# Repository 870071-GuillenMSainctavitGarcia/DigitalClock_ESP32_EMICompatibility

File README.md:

# DigitalClock_ESP32_EMICompatibility

A 2-layer custom hardware board designed in **KiCad 9.0** featuring dual isolated ground planes (`GND` and `GND1`), input noise filtering, an onboard 12V-to-5V buck regulator, and Wi-Fi capabilities for acquiring UTC time via NTP.

---

##  Features

- **ESP32 Microcontroller:** Integrated module layout with a dedicated antenna exclusion zone to maximize Wi-Fi & Bluetooth RF performance.
- **Dual Isolated Ground Planes:** Independent `GND` and `GND1` domains to prevent noise coupling across high-voltage input and digital control sections.
- **Power Management:**
  - **Input Filtering:** Common Mode Choke & Pi Filter ($C-L-C$) for supply line noise suppression.
  - **Buck Regulator:** High-efficiency $12\text{V} \to 5\text{V}$ DC-DC step-down switching converter (TSOT-23-8 footprint).
- **Peripherals & Debugging:**
  - Onboard I2C sensor interface with pull-up resistors (`SDA` / `SCL`).
  - Strategic Test Points (`12V_TP`, `5V_TP`, `3V3_TP`, `SDA_TP`, `SCL_TP`, `GND_TP`).
- **DFA / DFM Compliant:** 2-layer stackup optimized for JLCPCB manufacturing rules (0.15 mm minimum clearance).

---

##  Hardware Specifications

| Parameter | Value |
| :--- | :--- |
| **Input Voltage** | 12V DC |
| **Regulated Voltages** | 5V DC (Buck Converter Output), 3.3V DC (ESP32 LDO) |
| **PCB Stackup** | 2 Layers (`F.Cu` signal routing & components, `B.Cu` ground plane) |
| **EDA Software** | KiCad 9.0 |
| **Minimum Clearance** | 0.15 mm (6 mil) |
| **Drill Format** | Excellon Merged (PTH + NPTH) |
| **Gerber Format** | Extended Gerber RS-274X (Protel File Extensions) |

---

# PCB and Layout

- **Layer Architecture:**
  - **Top Layer (`F.Cu`):** Primary routing layer for SMD components, power distribution traces, and signal lines.
  - **Bottom Layer (`B.Cu`):** Dedicated low-impedance continuous ground plane for optimal return paths and EMI reduction.
- **Isolated Ground Planes (`GND` vs `GND1`):**
  - **`GND1` Domain:** Isolated ground fill surrounding the $12\text{V}$ power input, protection diode, and Pi filter stage to contain input switching noise.
  - **`GND` Domain:** Main system ground covering the buck regulator output stage, ESP32 module, and digital peripherals.
- **RF Antenna Keepout Zone:**
  - Full copper clearance on all layers directly underneath the ESP32 PCB antenna region to prevent RF attenuation and maintain maximum Wi-Fi/Bluetooth range.
- **Power Routing & Via Placement:**
  - Expanded track widths ($0.8\text{ mm} - 1.2\text{ mm}$) for $12\text{V}$ input, switching nodes, and $5\text{V}$ power rails.
  - Low-inductance ground vias placed in immediate proximity to SMD ground pads for direct bottom-layer stitching.
- **Design Rules (DRC):**
  - Optimized $0.15\text{ mm}$ ($6\text{ mil}$) trace clearance to accommodate high-density TSOT-23-8 IC footprints without manufacturing rule violations.
---

---

# Schematic

The schematic is divided into distinct functional blocks optimized for power integrity, noise isolation, and ease of debugging:

### 1. Power Input & Isolated Domain (`GND1`)
- **Input Terminal:** $12\text{V}$ DC main supply connection (`J2`).
- **Protection Stage:** Schottky diodes (`D1`, `D3`) providing reverse-polarity protection and transient voltage suppression.
- **Noise Filtering:** Dual-stage EMI filtering using a Common Mode Choke (`FL1`) and a Pi Filter ($C-L-C$) to prevent external noise from entering the board.

### 2. Step-Down Buck Converter ($12\text{V} \to 5\text{V}$)
- **Regulator Core:** High-efficiency DC-DC switching regulator (`U1`, TSOT-23-8 footprint).
- **LC Output Filter:** High-current power inductor (`L1`) paired with low-ESR ceramic capacitor banks (`C1`–`C16`) for low output voltage ripple under dynamic loads.

### 3. ESP32 Microcontroller Core (`U2`)
- **Main Processing Unit:** ESP32 module powered from the main $5\text{V}$ rail (converted to $3.3\text{V}$ via internal LDO).
- **Wireless Connectivity:** Optimized for Wi-Fi synchronization to fetch real-time UTC timestamps via NTP servers.

### 4. Sensor & Peripheral Interface
- **I2C Bus:** Dedicated MSOP-8 sensor interface (`U3`) and expansion header (`J3`) with integrated pull-up resistors (`RPullUp-SCL1`, `RPullUp-SDA1`).

### 5. Diagnostic Test Points
- Strategic test pads placed across key nets for oscilloscope and multimeter probing:
  - **Power Rails:** `12V_TP1`, `12VE_TP2`, `5V_TP5`, `3V3_TP7`
  - **Signals:** `SCL_TP9`, `SDA_TP8`
  - **Ground References:** `GND_TP3`, `GND_TP4`, `GND1_TP10`
---

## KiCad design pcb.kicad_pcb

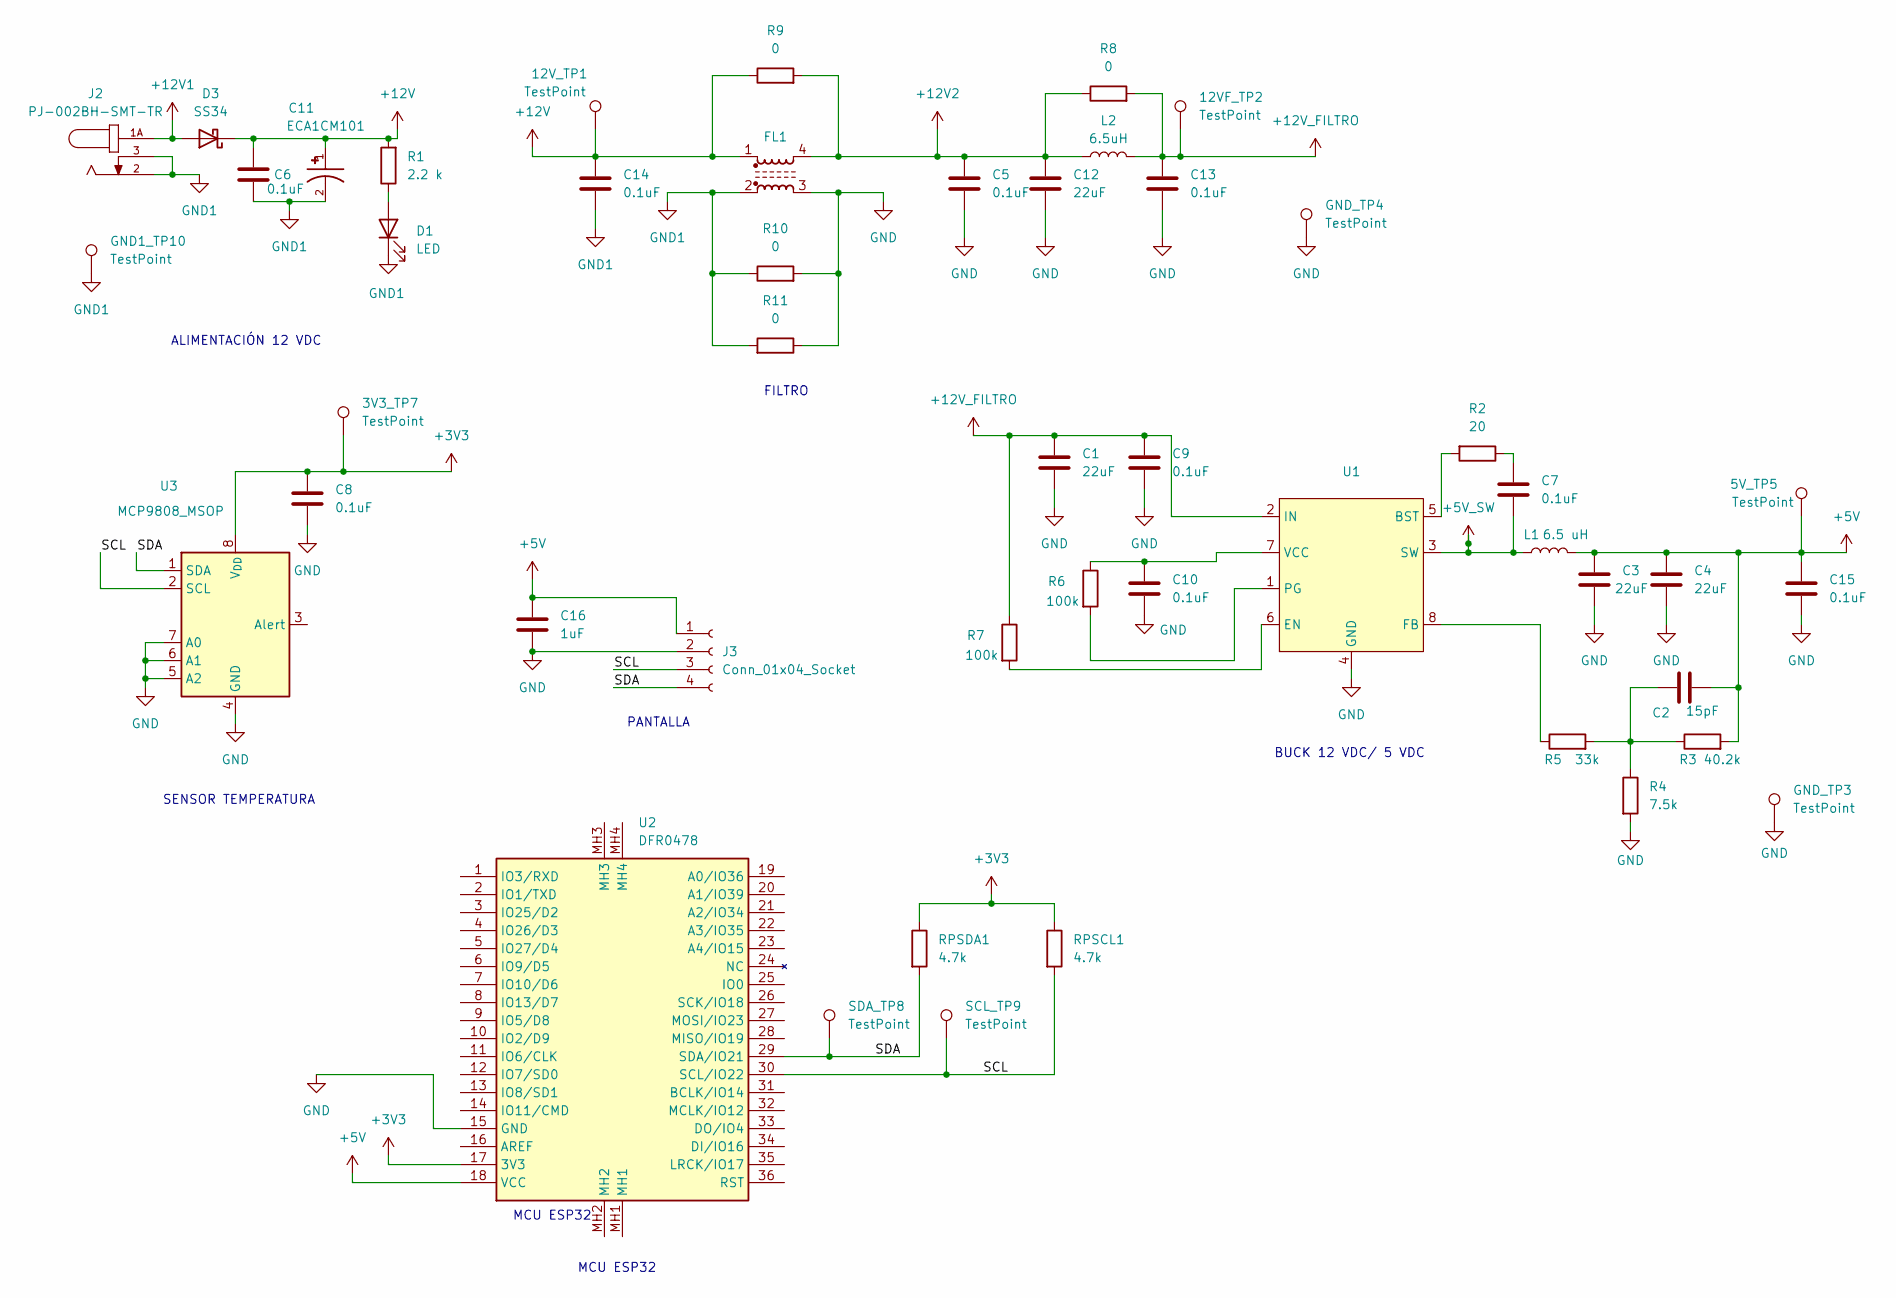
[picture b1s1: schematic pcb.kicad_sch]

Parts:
3V3_TP7, 5V_TP5, 12VF_TP2, 12V_TP1: TestPoint; TestPoint_THTPad_2.5x2.5mm_Drill1.2mm
C1, C3, C4, C12: 22uF; C_1206_3216Metric
C2: 15pF; C_1206_3216Metric
C5, C6, C7, C8, C9, C10, C13, C14, C15: 0.1uF; C_1206_3216Metric
C11: ECA1CM101; CP_Radial_D5.0mm_P2.00mm; PARTREV 20-DEC-19
C16: 1uF; C_1206_3216Metric
D1: LED; LED_1206_3216Metric
D3: SS34; D_SMA
FL1: Choke_CommonMode_FerriteCore_1324; L_CommonModeChoke_TDK_ACM7060
GND1_TP10: TestPoint; TestPoint_THTPad_2.5x2.5mm_Drill1.2mm
GND_TP3, GND_TP4: TestPoint; TestPoint_THTPad_2.5x2.5mm_Drill1.2mm
J2: PJ-002BH-SMT-TR; CUI_PJ-002BH-SMT-TR
J3: Conn_01x04_Socket; PinHeader_1x04_P2.54mm_Vertical
L1: 6.5 uH; L_Bourns_SRR1208_12.7x12.7mm
L2: 6.5uH; L_1206_3216Metric
R1: 2.2 k; R_1206_3216Metric
R2: 20; R_1206_3216Metric
R3: 40.2k; R_1206_3216Metric
R4: 7.5k; R_1206_3216Metric
R5: 33k; R_1206_3216Metric
R6, R7: 100k; R_1206_3216Metric
R8, R9, R10, R11: 0; R_1206_3216Metric
RPSCL1: 4.7k; R_1206_3216Metric
RPSDA1: 4.7k; R_1206_3216Metric
SCL_TP9: TestPoint; TestPoint_THTPad_2.5x2.5mm_Drill1.2mm
SDA_TP8: TestPoint; TestPoint_THTPad_2.5x2.5mm_Drill1.2mm
U1: TSOT-23-8
U2: DFR0478; FIREBEETLE_ESP32; Manufacturer_Part_Number DFR0478; Mouser Part Number 426-DFR0478
U3: MCP9808_MSOP; MSOP-8_3x3mm_P0.65mm

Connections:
+3V3: 3V3_TP7.1, C8.1, RPSCL1.1, RPSDA1.1, U2.17 (3V3), U3.8 (V_{DD})
+5V: 5V_TP5.1, C2.2, C3.1, C4.1, C15.1, C16.1, J3.1, L1.2, R3.2, U2.18 (VCC)
+5V_SW: C7.2, L1.1, U1.3 (SW)
+12V: 12V_TP1.1, C6.1, C11.1, C14.1, D3.1 (K), FL1.1, R1.2, R9.1
+12V1: D3.2 (A), J2.1A, J2.1B
+12V2: C5.1, C12.1, FL1.4, L2.1, R8.1, R9.2
+12V_FILTRO: 12VF_TP2.1, C1.1, C9.1, C13.1, L2.2, R7.1, R8.2, U1.2 (IN)
/SCL: J3.3, RPSCL1.2, SCL_TP9.1, U2.30 (SCL/IO22), U3.2 (SCL)
/SDA: J3.4, RPSDA1.2, SDA_TP8.1, U2.29 (SDA/IO21), U3.1 (SDA)
GND: C1.2, C3.2, C4.2, C5.2, C8.2, C9.2, C10.2, C12.2, C13.2, C15.2, C16.2, FL1.3, GND_TP3.1, GND_TP4.1, J3.2, R4.2, R10.2, R11.1, U1.4 (GND), U2.15 (GND), U3.4 (GND), U3.5 (A2), U3.6 (A1), U3.7 (A0)
GND1: C6.2, C11.2, C14.2, D1.1 (K), FL1.2, GND1_TP10.1, J2.2, J2.3, R10.1, R11.2
unnamed: C2.1, R3.1, R4.1, R5.2
unnamed: C7.1, R2.1
unnamed: D1.2 (A), R1.1
unnamed: R2.2, U1.5 (BST)
unnamed: R7.2, U1.6 (EN)
unnamed: R5.1, U1.8 (FB)
unnamed: R6.2, U1.1 (PG)
unnamed: C10.1, R6.1, U1.7 (VCC)

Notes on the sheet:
MCU ESP32
FILTRO
PANTALLA
BUCK 12 VDC/ 5 VDC
SENSOR TEMPERATURA
ALIMENTACIÓN 12 VDC

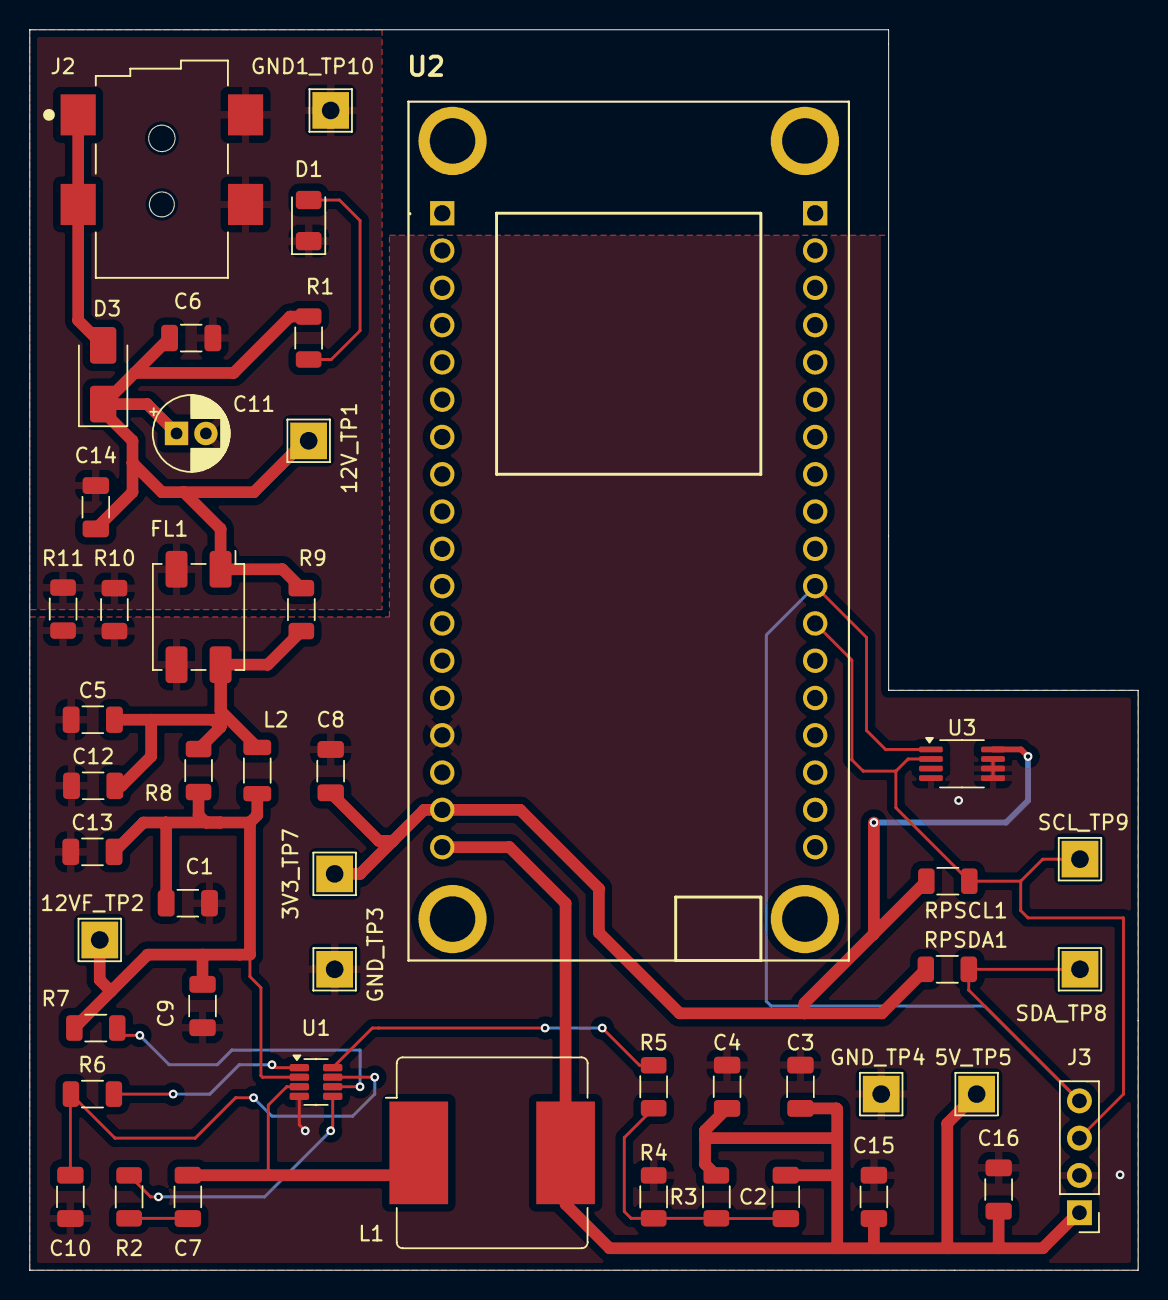
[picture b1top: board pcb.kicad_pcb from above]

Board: 2 copper layers, 75.5 x 84.5 mm, 48 parts (0 on the bottom side), 19 nets.
